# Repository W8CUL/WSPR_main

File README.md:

# WSPR_main

Standalone WSPR beacon using a Si5351 as the clock source.

Current PCB:

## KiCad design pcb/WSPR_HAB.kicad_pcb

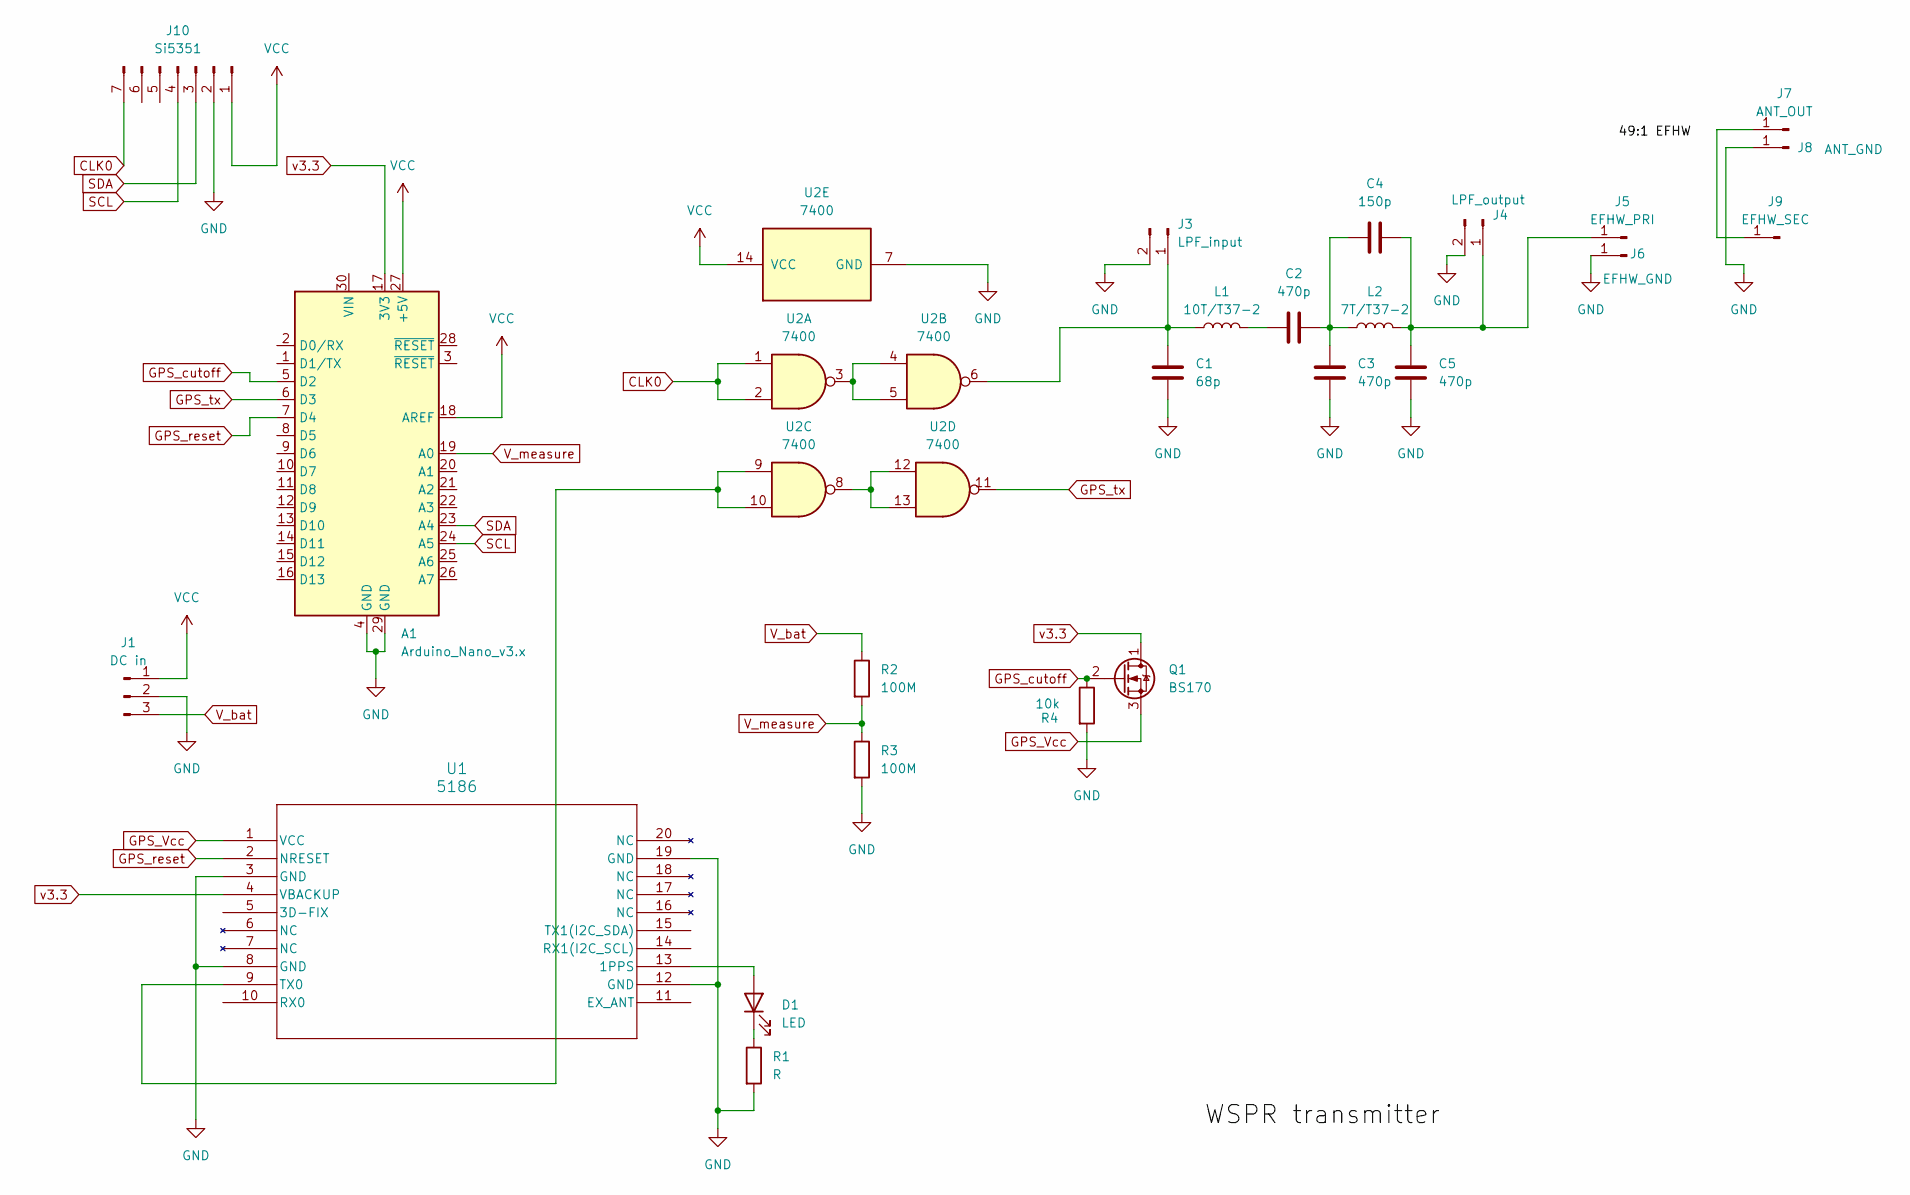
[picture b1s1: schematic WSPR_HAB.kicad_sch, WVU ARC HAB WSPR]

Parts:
A1: Arduino_Nano_v3.x; Arduino_Nano
C1: 68p; C_Axial_L3.8mm_D2.6mm_P7.50mm_Horizontal
C2, C3, C5: 470p; C_Axial_L3.8mm_D2.6mm_P7.50mm_Horizontal
C4: 150p; C_Axial_L3.8mm_D2.6mm_P7.50mm_Horizontal
D1: LED; LED_0805_2012Metric
J1: DC in; PinHeader_1x03_P2.54mm_Vertical
J3: LPF_input; PinHeader_1x02_P2.54mm_Vertical
J4: LPF_output; PinHeader_1x02_P2.54mm_Vertical
J5: EFHW_PRI; PinSocket_1x01_P2.54mm_Vertical
J6: EFHW_GND; PinSocket_1x01_P2.54mm_Vertical
J7: ANT_OUT; PinSocket_1x01_P2.54mm_Vertical
J8: ANT_GND; PinSocket_1x01_P2.54mm_Vertical
J9: EFHW_SEC; PinSocket_1x01_P2.54mm_Vertical
J10: Si5351; PinHeader_1x07_P2.54mm_Vertical
L1: 10T/T37-2; L_Toroid_Vertical_L10.0mm_W5.0mm_P5.08mm
L2: 7T/T37-2; L_Toroid_Vertical_L10.0mm_W5.0mm_P5.08mm
Q1: BS170; TO-92_Inline
R1: R; R_0805_2012Metric
R2, R3: 100M; R_Axial_DIN0204_L3.6mm_D1.6mm_P7.62mm_Horizontal
R4: 10k; R_Axial_DIN0204_L3.6mm_D1.6mm_P7.62mm_Horizontal
U1: 5186; CD-PA1616D_ADA
U2: 7400; DIP-14_W7.62mm_Socket

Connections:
CLK0: J10.7, U2.1, U2.2
GND: A1.4 (GND), A1.29 (GND), C1.2, C3.2, C5.1, J1.2, J3.2, J4.2, J6.1, J8.1, J10.2, R1.2, R3.2, R4.2, U1.3 (GND), U1.8 (GND), U1.12 (GND), U1.19 (GND), U2.7 (GND)
GPS_Vcc: Q1.3 (S), U1.1 (VCC)
GPS_cutoff: A1.5 (D2), Q1.2 (G), R4.1
GPS_reset: A1.7 (D4), U1.2 (NRESET)
GPS_tx: A1.6 (D3), U2.11
unnamed: C2.1, L1.2
unnamed: C2.2, C3.1, C4.1, L2.1
unnamed: D1.2 (A), U1.13 (1PPS)
unnamed: D1.1 (K), R1.1
unnamed: C1.1, J3.1, L1.1, U2.6
unnamed: C4.2, C5.2, J4.1, J5.1, L2.2
unnamed: J7.1, J9.1
unnamed: U1.9 (TX0), U2.9, U2.10
unnamed: U2.3, U2.4, U2.5
unnamed: U2.8, U2.12, U2.13
SCL: A1.24 (A5), J10.4
SDA: A1.23 (A4), J10.3
VCC: A1.18 (AREF), A1.27 (+5V), J1.1, J10.1, U2.14 (VCC)
V_bat: J1.3, R2.1
V_measure: A1.19 (A0), R2.2, R3.1
v3.3: A1.17 (3V3), Q1.1 (D), U1.4 (VBACKUP)

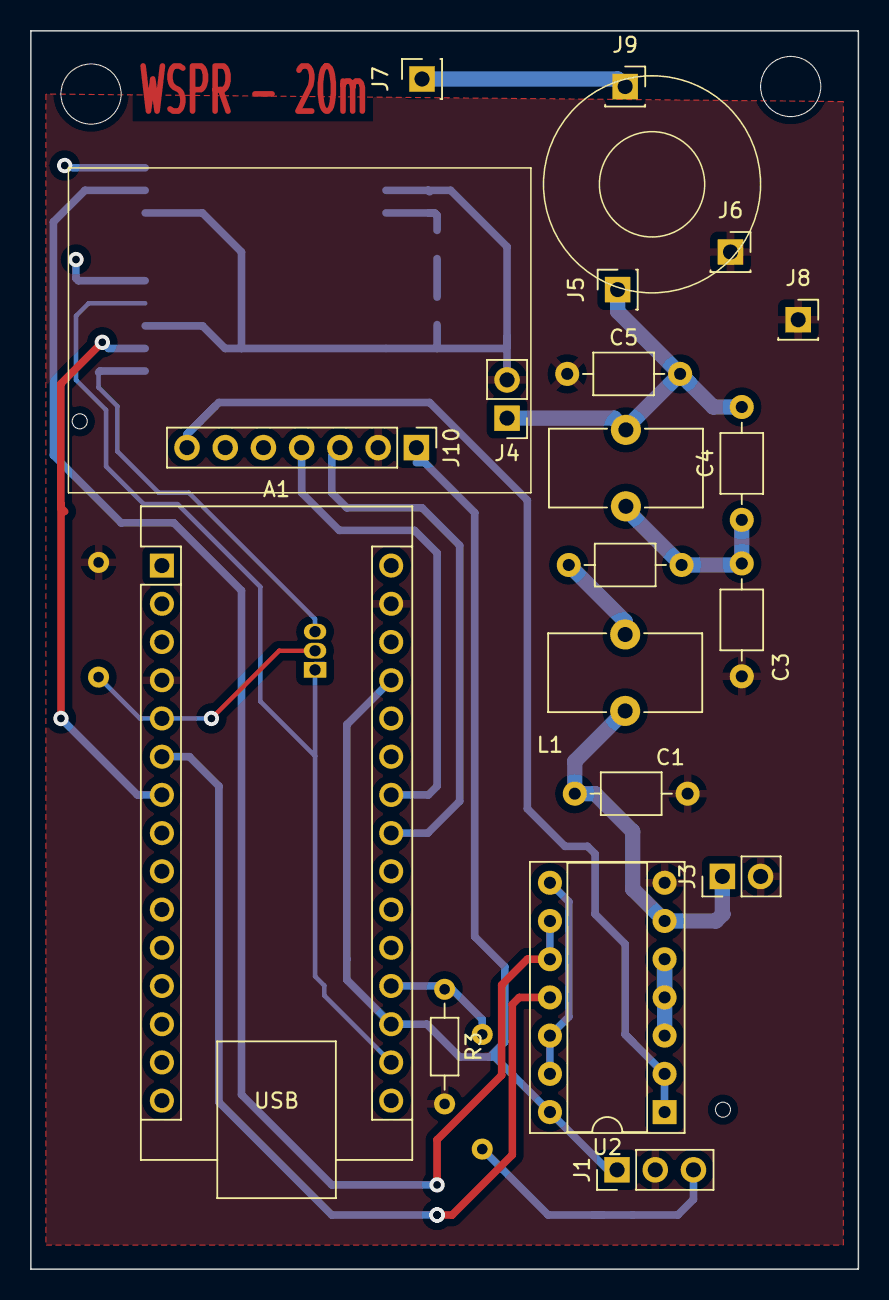
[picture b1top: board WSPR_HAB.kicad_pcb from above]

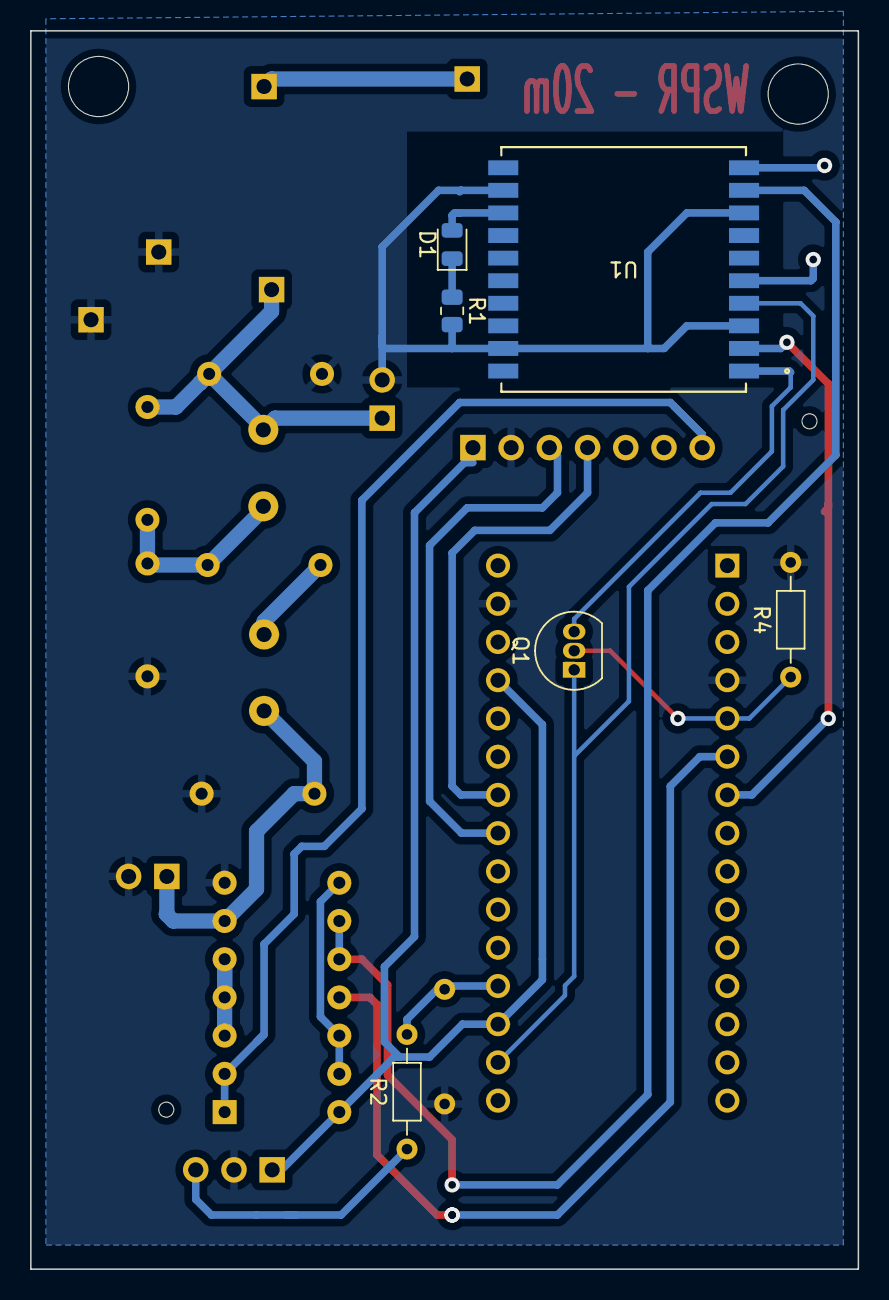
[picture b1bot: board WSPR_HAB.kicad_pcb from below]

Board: 2 copper layers, 55.0 x 82.3 mm, 25 parts (6 on the bottom side), 22 nets.

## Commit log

2025-02-07 added GPS read code
2025-02-07 added skeliton code for WSPR encode
2025-02-15 GPS synced FT8 output
2025-02-15 added untested code for grid generation
2025-02-23 bug fix for init packet with utc=0
2025-02-23 cleaned up unwanted modes from the code
2025-02-28 GPS grid update based on location - untested
2025-03-01 final flight v1 code. GPS location update and 4X2 grid update
2025-03-18 grid2loc program using python library
2025-03-19 made a PCB to use the high altitude rated GPS
2025-03-19 added v1.2 PCB with fixes to the torroid size
2025-03-25 added the Si5351 to the PCB
2025-03-25 added a mosfet and extra pins to the gps
2025-03-27 updated the GPS commands to work with a PD1616
2025-03-29 untested PD1616 min code added. 88% usage
2025-03-29 added WDT to fix the random hangs
